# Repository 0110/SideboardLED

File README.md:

# SideboardLED
Sprit: ollpe never dies

Another tiny project to control a WS2812 stripe via an Arduino based microcontroller.
## Hardware
* Atmega8
* 75 WS2812LEDs
* USB Serial converter

Programmer, e.g.:
* AVRISPmkii

## Software
### Arduino

In order to flash the software, select the following settings in Arduino:
* Tools | Board "Arduino NG or older"
* Tools | Processor "Atmega8"
* Sketch | Export Compiled Binary

In your arduino installtion, update the CPU frequency, as we are using the internal clock with 8Mhz.
Find the following file */hardware/arduino/avr/boards.txt*.
Inside the file, search for the chapter **Arduino NG or older w/ ATmega8** and add the following line:
```
atmegang.menu.cpu.atmega8.build.f_cpu=8000000L
```

### Avrdude
The flashing itself is done with **avrdude**:
```bash
avrdude -c AVRISPmkii -p m8 -u -U flash:w:SideboardLED.ino.standard.hex
```
Initial once the fuses must be burned:
```bash
avrdude -c avrispmkii -p atmega8 -U lfuse:w:0xe4:m -U hfuse:w:0xd9:m -U efuse:w:0xfc:m
```

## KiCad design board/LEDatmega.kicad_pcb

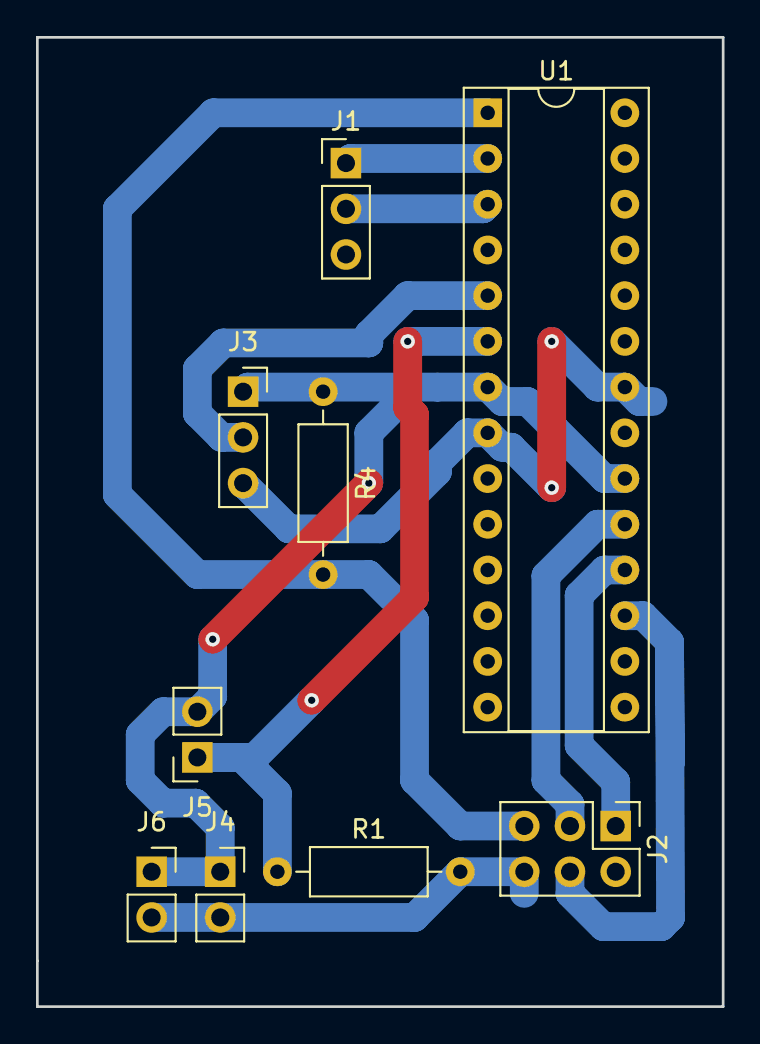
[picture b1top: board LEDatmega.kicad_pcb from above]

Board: 2 copper layers, 38.1 x 53.8 mm, 9 parts (0 on the bottom side), 10 nets.

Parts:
J1: Conn_01x03_Female; PinHeader_1x03_P2.54mm_Vertical
J2: Conn_02x03_Odd_Even; PinHeader_2x03_P2.54mm_Vertical
J3: Conn_01x03; PinSocket_1x03_P2.54mm_Vertical
J4, J5, J6: Conn_01x02_Male; PinSocket_1x02_P2.54mm_Vertical
R1: 100k; R_Axial_DIN0207_L6.3mm_D2.5mm_P10.16mm_Horizontal
R4: 10k; R_Axial_DIN0207_L6.3mm_D2.5mm_P10.16mm_Horizontal
U1: ATMEGA8-16PU; DIP-28_W7.62mm_Socket

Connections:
+5V: J3.1, J4.1, J5.2, J6.1, R4.1, U1.7, U1.20
GND: J1.3, J2.6, J3.3, J4.2, J6.2, R1.2, U1.8, U1.22
LED: J3.2, U1.5
MISO: J2.1, U1.18
MOSI: J2.4, U1.17
unnamed: J1.1, U1.2
unnamed: J1.2, U1.3
unnamed: J5.1, R1.1, U1.6
RESET: J2.5, R4.2, U1.1
SCK: J2.3, U1.19

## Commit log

2018-12-06 Initial version of the software
2018-12-06 Initial KiCAD project of the hardware board
2018-12-06 Described flashing
2018-12-06 Replaced USBtty connector with 6pin one
2018-12-07 Layouting done
2018-12-07 Generating of board
2018-12-07 Moved board in the upper left corner
2018-12-07 Clip for Sideboard mount
2018-12-07 Scale brightness of rainbow
2018-12-07 Included Button to start rainbow
2018-12-07 Documented the usage of the internal oscilator
2018-12-07 End mount of LED holder
2018-12-08 LED board house
2018-12-08 Added the generation of the hexfile in the docu
2018-12-08 Only 3pin connector for Serial interface
2018-12-08 Added export of schematics and board
2018-12-08 OpenHAB integration described
2018-12-10 Higher walls and bigger ground
2018-12-10 longer end plug
2018-12-10 Added board dimensions into layout
